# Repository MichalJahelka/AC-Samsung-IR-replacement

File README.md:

Wire replacement for SAMCUNG AC Remote Controller AR-EC03E/EH03E/EC03M/EH03M
IR protocol decoding, creating end sending example
IR protocol enconding for smart house realization

No protocol found for Samsung air condition IR control, so I had to catch communication with IR receiver (38 kHz) and decode it with MCU. I did not gues all bits, but the biggest part of protocol was decoded. For decoding is used PIC18F47K40, sends data throug serial line to terminal for display at PC. Program IRprotokolSamsungAC.X is written in MPLAB X, uses free compiler, has CZECH comments (so translator can be handy).
IRprotokolSamsungAC.X can decode protocols and after uncomment
//TransmittPacket(Paket,Delka);
//while(1);
can emulate one time data sending.
I tested it with IR LED, so pin with 38 kHz modulation is there too.

At second part KlimatizaceSamsung.X is practical usage. It uses iDum protocol for communication with control unit, data are passed to CreatePaket function and then created packet is send to output. It does not using IR LED, it connects throug optocoupler to IR receiver at AC unit, so modulation is not needed. Practilal realisation has schematic and PCB.

There is no problem to use it in another own device. Important is creating packet and sending it:
When data arrives:
if(Zprava.Data.Obsah.ZArray.Data[0]==rksCommand)
{
  Opt=(TOptions *)&Zprava.Data.Obsah.ZArray.Data[4];
  Swing=(TSwing *)&Zprava.Data.Obsah.ZArray.Data[6];
  i=CreatePaket(SamsungPaket,Zprava.Data.Obsah.ZArray.Data[1],    // Mode
                             Zprava.Data.Obsah.ZArray.Data[2],    // Temperature
                             Zprava.Data.Obsah.ZArray.Data[3],    // Fan
                             *Opt,                                // Options
                             *Swing,                              // Swing
                             Zprava.Data.Obsah.ZArray.Data[7],    // Zone
                             Zprava.Data.Obsah.ZArray.Data[8]);   // Direction
  VysliAccept();
  TransmittPacket(SamsungPaket,i);
  break;
}

And sending is automatic with TMR5 interrupt:
PIE4=0b00010011;      // TMR5IE,TMR2IE,TMR1IE
IPR4=0b00010001;      // TMR5 (Samsung transmitt), TMR1 (iDum) High priority

void __interrupt() Preruseni(void)
{
  iDumProcessIntr();
  TransmittBlockInterrupt(); // here is sending realized
}

CreatePaket, TransmittPacket and TransmittBlockInterrupt functions are parts of SamsungIR library.

Schematic is in KiCAD, extended documents are in CZECH language, use transaltor if you want.

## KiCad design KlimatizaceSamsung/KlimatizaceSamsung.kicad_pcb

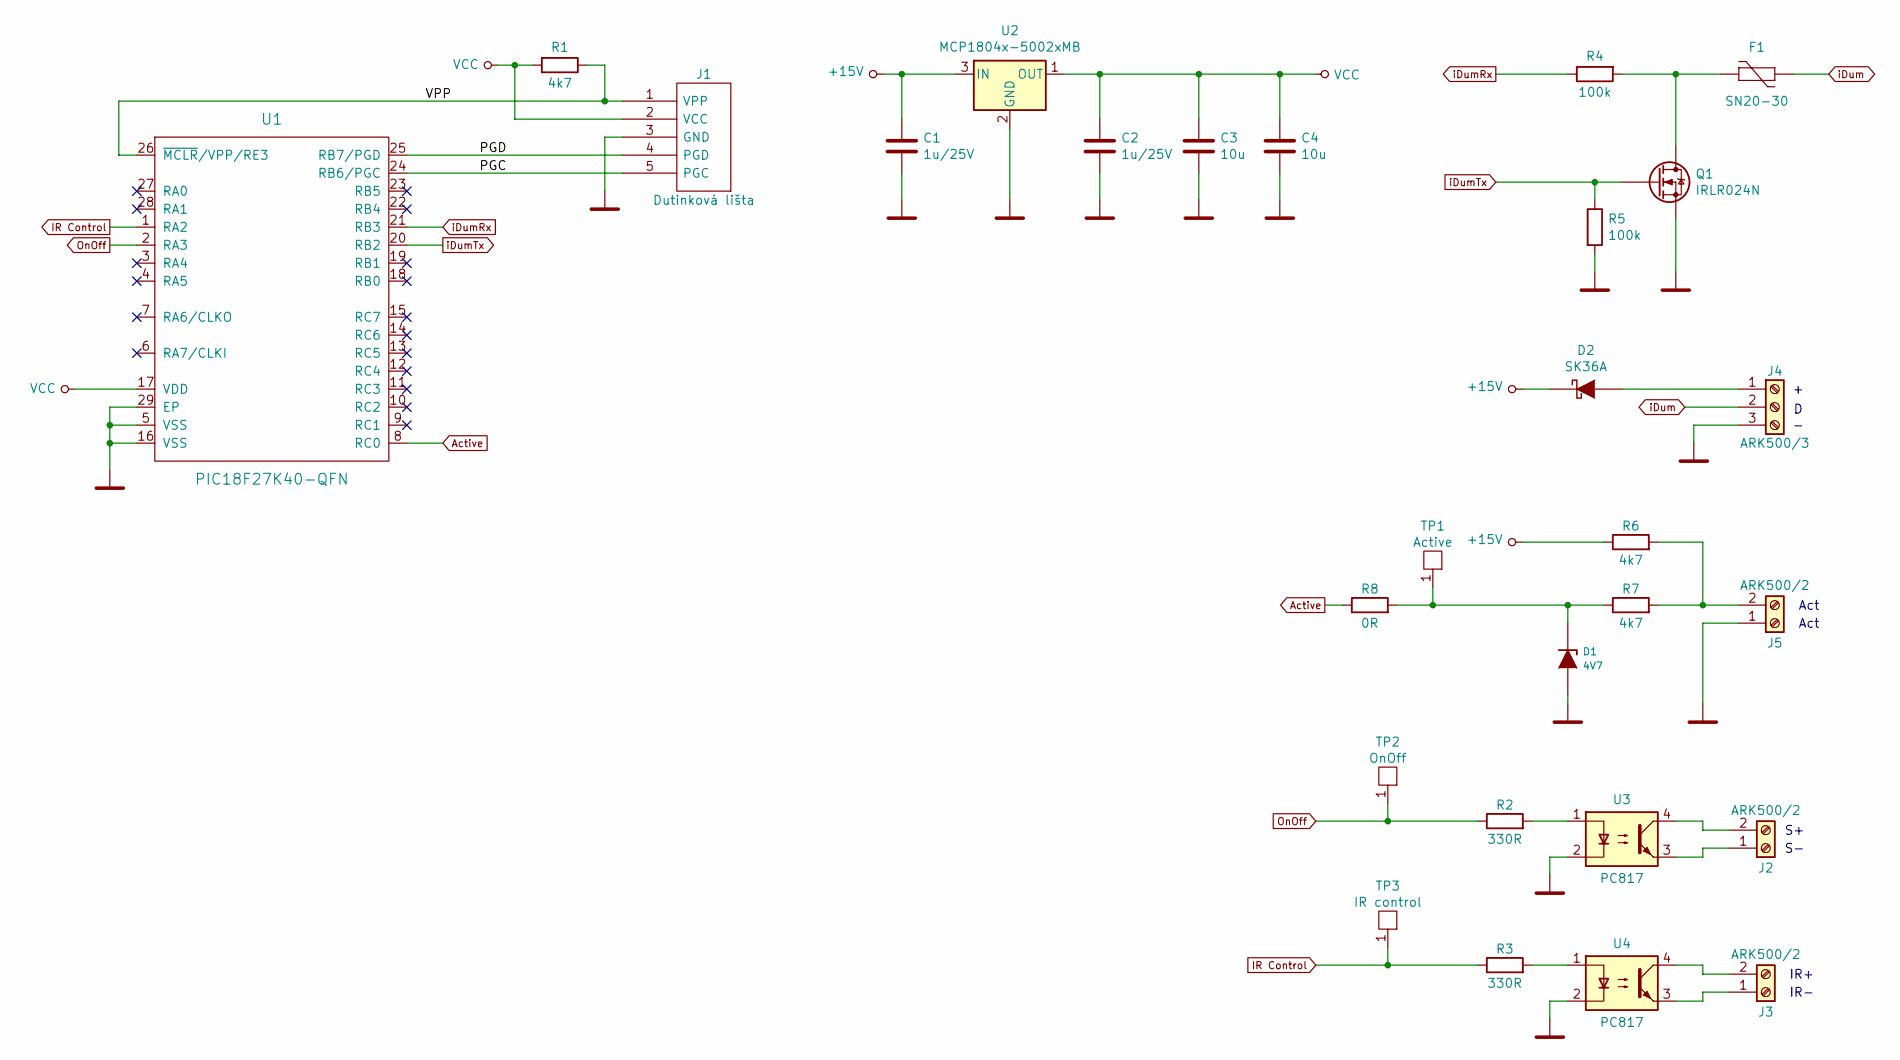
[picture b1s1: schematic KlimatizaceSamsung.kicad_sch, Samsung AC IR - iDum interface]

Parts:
C1, C2: 1u/25V; C_0805_2012Metric
C3, C4: 10u; C_0805_2012Metric
D1: 4V7; D_MiniMELF
D2: SK36A; D_SMA_Handsoldering
F1: SN20-30; PTC_SMD1206
J1: Dutinková lišta; PinSocket_1x05_P2.54mm_Vertical
J2, J3, J5: ARK500/2; DG301-5.0-2-LargePads
J4: ARK500/3; DG301-5.0-3-LargePads
Q1: IRLR024N; DPAKGDS
R1, R6, R7: 4k7; R_0805_2012Metric
R2, R3: 330R; R_0805_2012Metric
R4, R5: 100k; R_0805_2012Metric
R8: 0R; R_0805_2012Metric
TP1: Active; TP2
TP2: OnOff; TP2
TP3: IR control; TP2
U1: PIC18F27K40-QFN; QFN-PIC18F27K40
U2: MCP1804x-5002xMB; SOT-89-3
U3, U4: PC817

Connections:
+15V: C1.1, D2.1 (K), R6.1, U2.3 (IN)
/PGC: J1.5 (PGC), U1.24 (RB6/PGC)
/PGD: J1.4 (PGD), U1.25 (RB7/PGD)
/VPP: J1.1 (VPP), R1.1, U1.26 (~MCLR/VPP/RE3)
Active: R8.1, U1.8 (RC0)
GND: C1.2, C2.2, C3.2, C4.2, D1.2, J1.3 (GND), J4.3, J5.1, Q1.S, R5.2, U1.5 (VSS), U1.16 (VSS), U1.29 (EP), U2.2 (GND), U3.2, U4.2
IR Control: R3.1, TP3.1 (&1), U1.1 (RA2)
unnamed: D2.2 (A), J4.1
unnamed: F1.2, Q1.D, R4.2
unnamed: J2.1, U3.3
unnamed: J2.2, U3.4
unnamed: J3.1, U4.3
unnamed: J3.2, U4.4
unnamed: J5.2, R6.2, R7.2
unnamed: R2.2, U3.1
unnamed: R3.2, U4.1
unnamed: D1.1, R7.1, R8.2, TP1.1 (&1)
OnOff: R2.1, TP2.1 (&1), U1.2 (RA3)
VCC: C2.1, C3.1, C4.1, J1.2 (VCC), R1.2, U1.17 (VDD), U2.1 (OUT)
iDum: F1.1, J4.2
iDumRx: R4.1, U1.21 (RB3)
iDumTx: Q1.G, R5.1, U1.20 (RB2)

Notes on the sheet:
IR-
IR+
Act

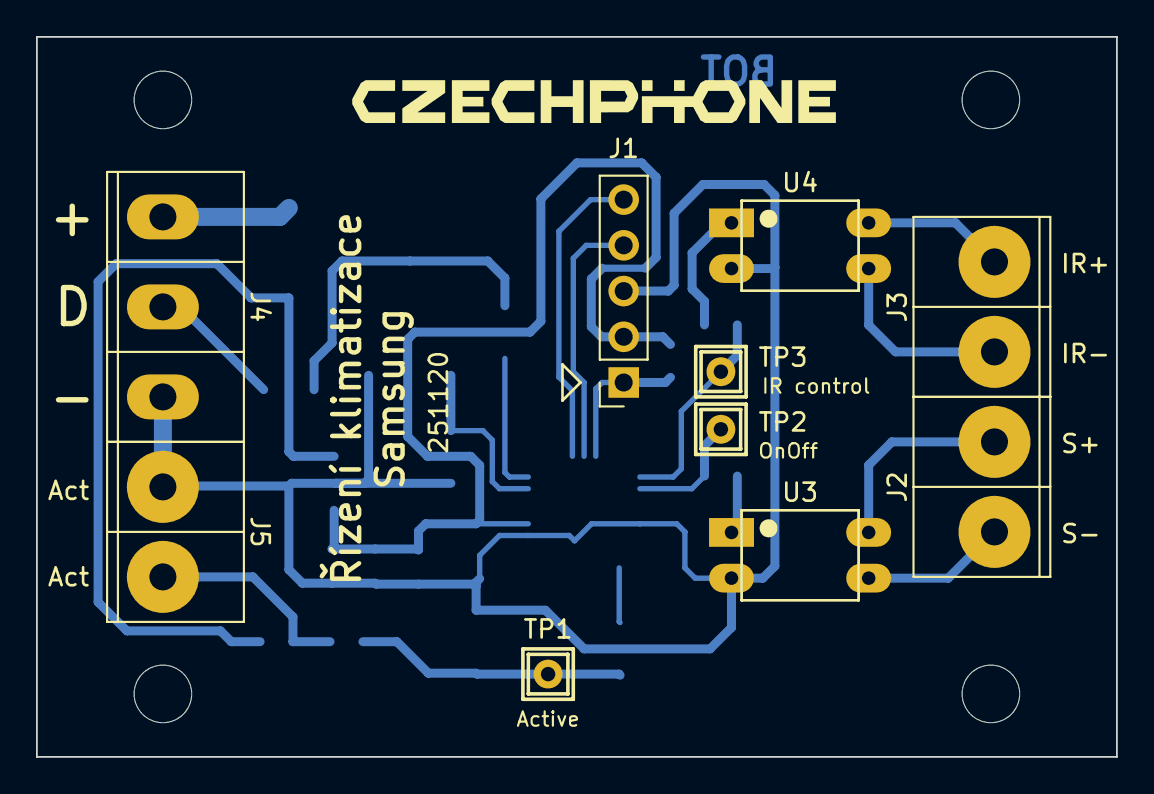
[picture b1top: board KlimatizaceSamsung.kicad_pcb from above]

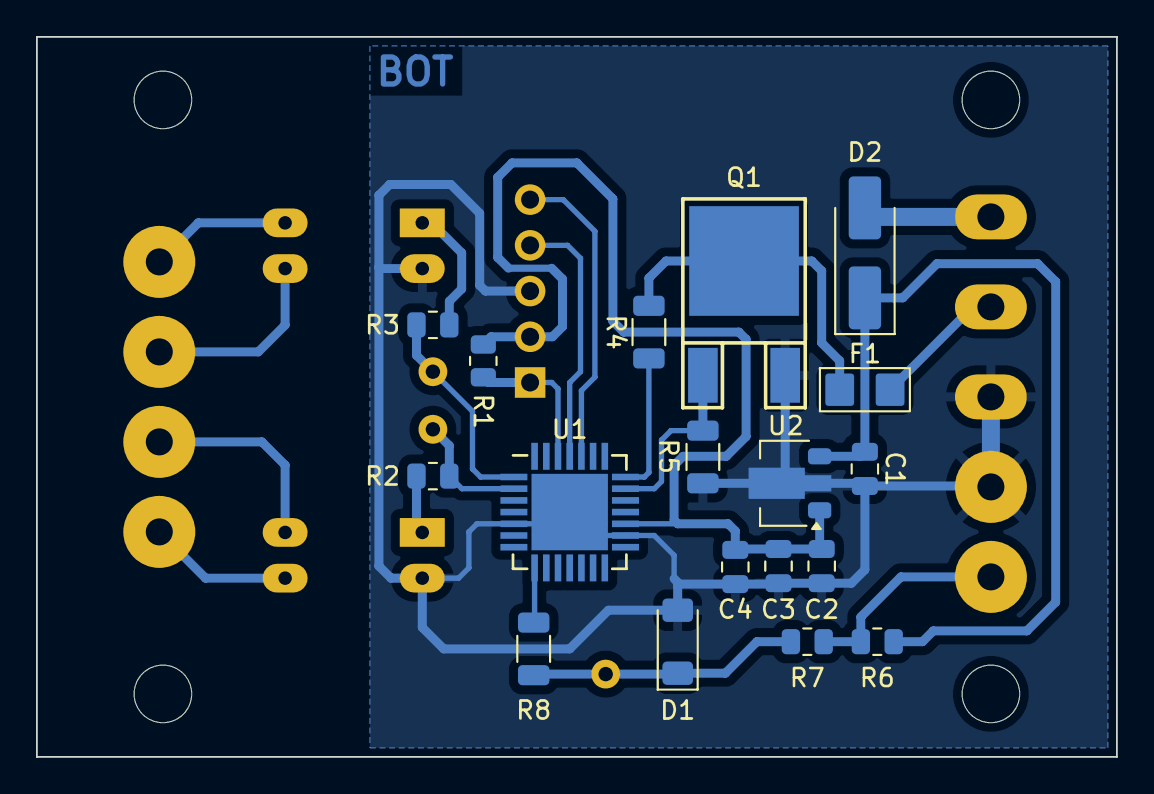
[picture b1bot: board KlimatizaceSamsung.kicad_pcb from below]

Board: 2 copper layers, 60.0 x 40.0 mm, 31 parts (18 on the bottom side), 22 nets.

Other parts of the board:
Dira3mmNTPH, Dira3mmNTPH#2, Dira3mmNTPH#3: Val**; Dira3,2mmNTPH

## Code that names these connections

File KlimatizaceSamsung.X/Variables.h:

/*
 * Definice a proměnné pro řízení klimatizace Samsung
 */

#ifndef VARIABLES_H
#define	VARIABLES_H

#ifdef	__cplusplus
extern "C"
{
  #endif

  #include "../../DevTypes.h"

  #define MaxBufLen       64
  #define DevType         dtKlimatizaceSamsung

  #include "../../Zpravy.h"

  #define Cas1ms              (0xFFFF-CrystalFreq/4000+1) // (0x10000-CrystalFreq/4000) dává hlášku Arithmetic overflow in constant expression
  #define CasScanu            (Cas1ms/2+0x8000)

  #define Rx              PORTCbits.RC7
  #define Tx              LATBbits.LATB2
  #define TrisTx          TRISBbits.TRISB2
  #define IRControl       LATAbits.LATA2
  #define OnOff           LATAbits.LATA3
  #define Active          PORTCbits.RC0
  #define AccessIO        PORTBbits.RB7
  
  
  #define iDumTxIO()      { RB2PPS = 0x00; }               // LATB2 -> RB2
  #define iDumTxUART()    { RB2PPS = 0x09; }               // TX1   -> RB2
  
  // Pozice konfigurace v paměti EEPROM
  #define EEPROM_DevID            0u
  #define EEPROM_CasZakmitu       EEPROM_DevID+1
  #define EEPROM_Popis            8u
  
  // Příkazy pro modul řízení klimatizace Samsung
  #define rksPower                0x01  // Sepnutí vypínače
  #define rksStatus               0x02  // Změna stavu
  #define rksCommand              0x03  // Příkaz (emulace DO)
  
  // Proměnné pro systém iDům
  TZprava Docasna,Zprava,Vysilani,TempZprava,ZalohaZpravy;
  __near unsigned char Cas,EECheckSum;
  __near unsigned char PoziceZpravy,PrijatyZnak,DevID,Configuring,WaitingTime;
  __near bit PrijimamData,ZpracovavamData,ZpravaPrijata,VysilaniSelhalo,Vysilam;
  __near bit ZpravaVyslana,Sleeping,ByloPreruseni1,ByloPreruseni2;
  unsigned char RandID[4];
  __persistent unsigned int LastRand;   // Náhodné číslo
  __persistent unsigned int IDV_OK,IDV_Sent,IDV_Fail,IDV_Error,IDV_Conflict,IDV_Reset;
  
  // Proměnné specifické pro hardware
  unsigned int CasDelay;              // Čekání pro čekací smyčku
  unsigned char CasZakmitu;           // Čas zákmitů
  unsigned char Vstup;                // Stav vstupů
  unsigned char StaryVstup;           // Původní stav vstupů
    
  bit BylaZmenaVstupu;                // Došlo ke změně vstupu
  
  void ReloadEEPROM(void);

  #ifdef	__cplusplus
}
#endif

#endif	/* VARIABLES_H */

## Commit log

2026-01-01 First release
